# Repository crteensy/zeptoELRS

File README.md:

# zeptoELRS
a small ELRS receiver

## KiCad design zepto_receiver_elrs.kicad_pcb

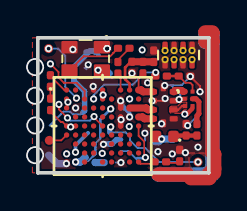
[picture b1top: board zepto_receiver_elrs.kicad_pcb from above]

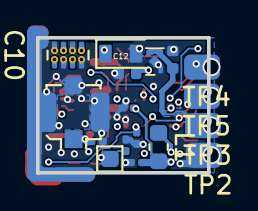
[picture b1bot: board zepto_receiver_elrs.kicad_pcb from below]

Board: 4 copper layers, 9.5 x 7.5 mm, 39 parts (17 on the bottom side), 29 nets.

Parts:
C1, C2, C6: 1µF; C_0201_0603Metric_dense
C3, C5: 10µF; L_0402_1005Metric_dense
C8: 100nF; C_0201_0603Metric_dense
C10: 2.2uF; 0805_low_esl_cap_avx
C11: 2.2uF; 0805_low_esl_cap_avx_w_via_dense
C12: 100uF; AVX_S_CASE
C13: 1nF; C_0201_0603Metric_dense
C14: 10pF; C_0201_0603Metric_dense
C15: 68pF; C_0201_0603Metric_dense
C18: 33pF; C_0201_0603Metric_dense
C21, C26: 3.3pF; C_0201_0603Metric_dense
D1: LED_BLUE; LED_0201_0603Metric
D2: LED_WHITE; LED_0201_0603Metric
FID1, FID2, FID3: Fiducial; Fiducial_0.5mm_Dia_1mm_Outer
J1: u.fl; U.FL_Molex_MCRF_73412-0110_Vertical
L1: 15µH; L_0603_1608Metric
L2: 33nH; R_0201_0603Metric_dense
L6: 8.7nH; L_0402_1005Metric_dense
R1, R2: 270R; R_0201_0603Metric_dense
R4: 10k; R_0201_0603Metric_dense
R5: 100R; R_0201_0603Metric_dense
R6: 220R; R_0201_0603Metric_dense
TP1: Pad 1x1mm; TestPoint_Pad_1.0x1.0mm
TP2, TP3, TP4, TP5: Pad 1.5x1.5mm; TestPoint_Pad_1.5x2mm
U1: STM32WLE5JBI6
U2: NCP160; UDFN-4_1x1mm_P0.65mm
U3: BGS12PL6E6327XTSA1
U4: 0900FM15D0039
U5: ECS-TXO-25CSMV-320-AM-TR; ECS-TXO-25CSMV-320-AM-TR_reduced_pads

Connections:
3.3-5V_IN: C3.1, TP3.1, U2.3, U2.4
+3V3: C5.1, C10.1, C11.2, C12.1, D1.2, U1.A2, U1.A5, U1.A7, U1.A8, U1.B5, U1.E2, U1.E8, U1.E9, U1.H5, U1.H8, U2.1, U3.4, U5.4
Boot0: R4.2, TP1.1, U1.J5
GND: C1.2, C2.2, C3.2, C5.2, C6.2, C8.2, C10.2, C11.1, C12.2, C13.1, C15.2, C21.2, C26.2, D2.1, J1.2, R4.1, TP2.1, U1.A1, U1.B7, U1.D9, U1.E3, U1.G5, U1.G6, U1.G7, U1.G8, U1.H6, U2.2, U2.5, U3.2, U4.2, U4.5, U4.7, U4.9, U4.10, U5.1, U5.2
LED1: R1.1, U1.A9
LED2: R2.2, U1.J1
NRST: C8.1, FID1.1, U1.F5
unnamed: C13.2, R5.1, U3.6
unnamed: C14.1, R6.2
unnamed: C18.1, U3.5
unnamed: C18.2, C21.1, L6.1
unnamed: C26.1, J1.1, L6.2
unnamed: D1.1, R1.2
unnamed: D2.2, R2.1
unnamed: L1.1, U1.B2
unnamed: L2.2, U1.J9, U4.1
unnamed: R6.1, U5.3
RFI: U3.3, U4.6
RFI_N: U1.H7, U4.3
RFI_P: U1.J6, U4.4
RFO: U3.1, U4.8
RFSW_CRTL: R5.2, U1.D8
SWDCLK: FID3.1, U1.A4
SWDIO: FID2.1, U1.B8
UART_RX: TP4.1, U1.C8
UART_TX: TP5.1, U1.D6, U1.E5
VDDRF1V5: C1.1, C6.1, L1.2, U1.B1, U1.F7
VR_PA: C2.1, C15.1, L2.1, U1.H9
XI: C14.2, U1.G9

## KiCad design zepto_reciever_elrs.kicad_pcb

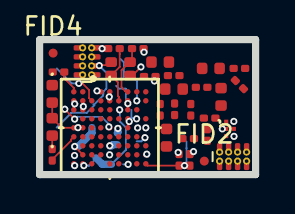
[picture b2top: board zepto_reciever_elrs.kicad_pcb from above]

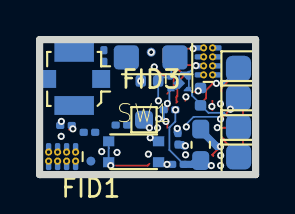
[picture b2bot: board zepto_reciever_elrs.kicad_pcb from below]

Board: 4 copper layers, 12.0 x 7.5 mm, 54 parts (23 on the bottom side), 29 nets.

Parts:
C1, C2, C4, C6: 1µF; C_0201_0603Metric
C3, C5: 10µF; C_0402_1005Metric
C7, C10: 2.2uF; 0805_low_esl_cap_avx_w_via
C8: 100nF; C_0201_0603Metric
C9, C11: 2.2uF; 0805_low_esl_cap_avx
C12: 100uF; CP_EIA-3216-18_Kemet-A
C13: 1nF; C_0201_0603Metric
C14, C24: 1.2pF; C_0201_0603Metric
C15: 2.2pF; C_0201_0603Metric
C16: 5.6pF; C_0201_0603Metric
C17, C23: 6.2pF; C_0201_0603Metric
C18: 33pF; C_0201_0603Metric
C19: 68pF; C_0201_0603Metric
C20: 2.7pF; C_0201_0603Metric
C21, C26: 3.3pF; C_0201_0603Metric
C22: 3.6pF; C_0201_0603Metric
C25: 1pF; C_0201_0603Metric
D1: LED_BLUE; LED_0402_1005Metric
D2: LED_WHITE; LED_0402_1005Metric
FID1, FID2, FID3, FID4: Fiducial; Fiducial_0.5mm_Dia_1mm_Outer
J1: u.fl; U.FL_Molex_MCRF_73412-0110_Vertical
L1: 15µH; L_0603_1608Metric_Pad1.05x0.95mm_HandSolder
L2: 33nH; L_0402_1005Metric
L3: 3.6nH; L_0402_1005Metric
L4: 11nH; L_0402_1005Metric
L5, L6: 8.7nH; L_0402_1005Metric
R1, R2: 270R; R_0201_0603Metric
R3, R4: 10k; R_0201_0603Metric
R5: 100R; R_0201_0603Metric
SW1: SW_Push; EVPBL9A2B000
TP1: Pad 1x1mm; TestPoint_Pad_1.0x1.0mm
TP2, TP3, TP4, TP5: Pad 1.5x1.5mm; TestPoint_Pad_1.5x1.5mm
U1: STM32WLE5JBI6
U2: NCP160; UDFN-4_1x1mm_P0.65mm
U3: BGS12PL6E6327XTSA1
Y1: 32MHz; XTAL_ECS-320-8-47-CKM-TR

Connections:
3.3-5V_IN: C3.1, TP3.1, U2.3, U2.4
+3V3: C5.1, C7.1, C9.2, C10.1, C11.2, C12.1, D1.2, D2.2, R3.2, U1.A2, U1.A5, U1.A7, U1.A8, U1.B5, U1.E2, U1.E8, U1.E9, U1.H5, U1.H8, U2.1, U3.4
BIND_BUT: C4.1, R3.1, SW1.1, U1.J1
Boot0: R4.2, TP1.1, U1.J5
GND: C1.2, C2.2, C3.2, C4.2, C5.2, C6.2, C7.2, C8.2, C9.1, C10.2, C11.1, C12.2, C13.1, C14.1, C16.1, C17.2, C20.1, C21.2, C23.2, C24.2, C25.1, C26.2, J1.2, R4.1, SW1.2, TP2.1, U1.A1, U1.B7, U1.B8, U1.D9, U1.E3, U1.G5, U1.G6, U1.G7, U1.G8, U1.H6, U2.2, U2.5, U3.2, Y1.2, Y1.4
LED1: R1.1, U1.A9
LED2: R2.1, U1.A4
unnamed: C8.1, U1.F5
unnamed: C13.2, R5.1, U3.6
unnamed: C14.2, C15.2, L2.2, L3.1, U1.J9
unnamed: C15.1, C16.2, C19.2, L3.2
unnamed: C18.1, U3.5
unnamed: C18.2, C21.1, L6.1
unnamed: C19.1, L5.1
unnamed: C26.1, J1.1, L6.2
unnamed: D1.1, R1.2
unnamed: D2.1, R2.2
unnamed: L1.1, U1.B2
RF1: C22.1, C25.2, U3.3
RF2: C24.1, L5.2, U3.1
RFI_N: C20.2, L4.2, U1.H7
RFI_P: C22.2, L4.1, U1.J6
RFSW_CRTL: R5.2, U1.J2
UART_RX: TP4.1, U1.C8
UART_TX: TP5.1, U1.E5
VDDRF1V5: C1.1, C6.1, L1.2, U1.B1, U1.F7
VR_PA: C2.1, L2.1, U1.H9
XI: C17.1, U1.G9, Y1.3
XO: C23.1, U1.F8, Y1.1

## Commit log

2021-03-10 added pdf schematic
2021-03-10 Routed half of the Layout, changed a few pins
2021-03-10 updated layout, adjusted courtyards, updated schematic pdf
2021-03-11 Added Integrated filter and TXCO
2021-03-11 Saved the routed layout with discretes in own file
2021-03-11 new layout with integrated passives and TCXO
2021-03-11 update dimensions in layout
2021-03-11 updated silk screen
2021-03-12 Shrinked down reciever to 9.5x7.5mm
2021-03-12 connect SWDIO in layout
2021-03-13 adjust schematic, further layout work
2021-03-13 update schematic and layout
2021-03-13 moved a few components, checked pinout
2021-03-13 update sch, pdf and layout, add 3d views
2021-03-14 Created panels, changed sideplating, added a few comments
2021-03-14 added bom pdf and ods
2021-03-14 update 3d views
2021-05-29 add cubemx for blinky
